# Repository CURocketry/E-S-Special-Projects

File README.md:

# E&S Special Projects
This is where all the non-payload or research related E&S projects go. Below you can find a list and short description of all projects in this repo. 
## Airbrake
All E&S work on the airbrake project. 
## ES Datalogger
All purpose datalogger for model rockets. Logs data from a 9-DoF IMU and altimeter and saves it to an SD card. Powered by a 3.7V LiPo battery.
## SAMD21 Minimal
Minimal circiut that has all the hardware needed to run and program a SAMD21 chip. Be sure to add a USB header if you want to program via USB!

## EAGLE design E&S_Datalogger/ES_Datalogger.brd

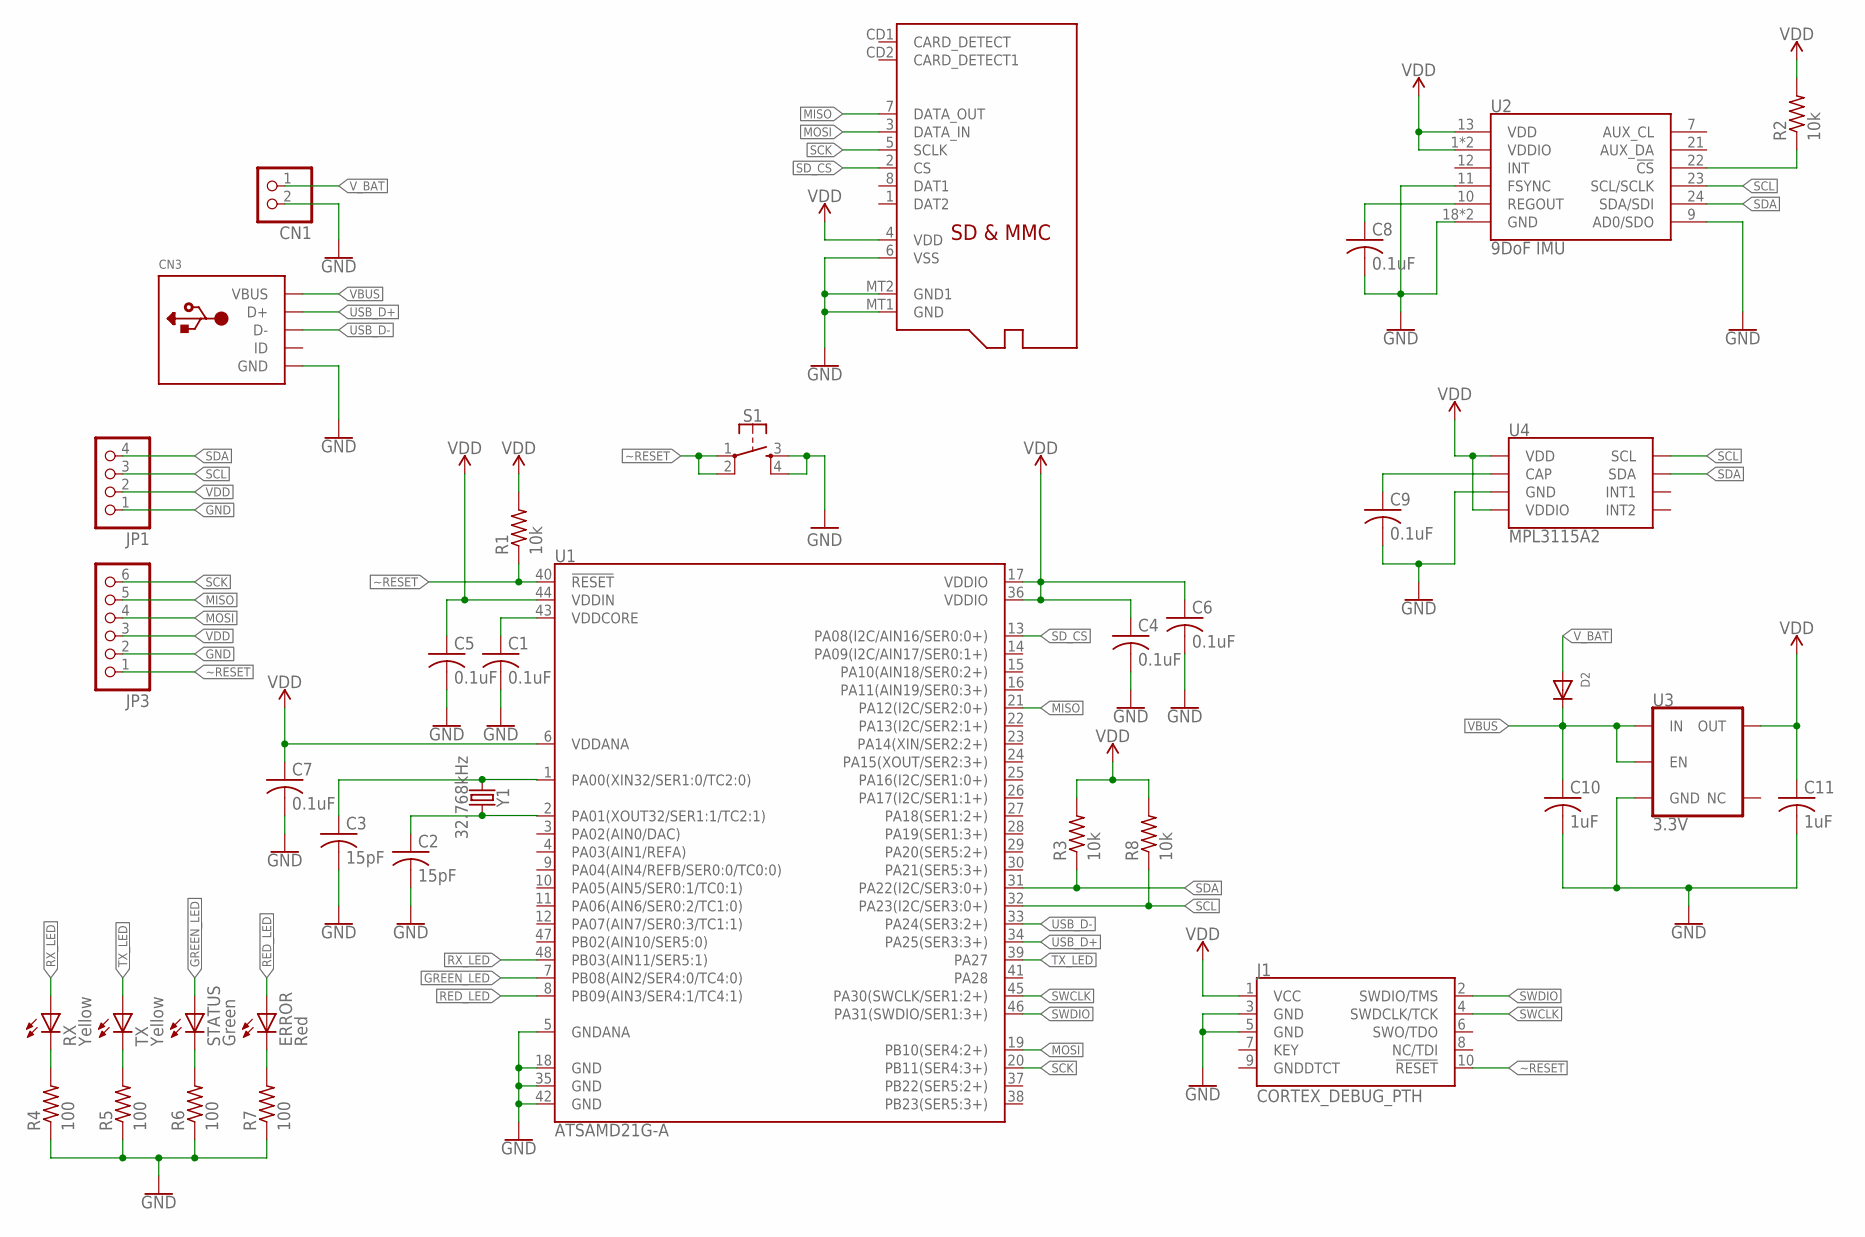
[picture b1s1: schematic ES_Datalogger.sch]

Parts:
C1, C4, C5, C6, C7, C8, C9: 0.1uF; C0805
C2, C3: 15pF; C0805
C10, C11: 1uF; C0805
CN1: JST_2PIN-SMT; JST-PH-2-SMT
CN3: USBMOLEX; USB-MINIB-THM-MOLEX
D2: DIODE_SOD-123FL; SOD-123FL
ERROR: Red; CHIPLED_0805
J1: CORTEX_DEBUG_PTH; 2X5-PTH-1.27MM
JP1: PINHD-1X4; 1X04
JP3: PINHD-1X6; 1X06
R1, R2, R3, R8: 10k; R0805
R4, R5, R6, R7: 100; R0805
RX: Yellow; CHIPLED_0805
S1: MOMENTARY-SWITCH-SPST-2-SMD-5.2MM; TACTILE_SWITCH_SMD_5.2MM
STATUS: Green; CHIPLED_0805
TX: Yellow; CHIPLED_0805
U1: ATSAMD21G-A; TQFP-48
U2: 9DoF IMU; QFN24-3X3
U3: 3.3V; SOT23-5
U4: MPL3115A2; LGA-8-5X3
U$1: MICROSD
Y1: 32.768kHz; CRYSTAL-SMD-MC-146

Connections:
GND: C1.2, C2.2, C3.2, C4.2, C5.2, C6.2, C7.2, C8.2, C9.2, C10.2, C11.2, CN1.2 (1), CN3.GND, J1.3 (GND), J1.5 (GND), JP1.1, JP3.2, R4.1, R5.1, R6.1, R7.1, S1.3, S1.4, U1.5 (GNDANA), U1.18 (GND), U1.35 (GND), U1.42 (GND), U2.9 (AD0/SDO), U2.11 (FSYNC), U2.18 (GND), U2.20 (GND), U3.2 (GND), U4.3 (GND), U$1.6 (VSS), U$1.MT1 (GND), U$1.MT2 (GND1)
GREEN_LED: STATUS.A, U1.7 (PB08(AIN2/SER4:0/TC4:0))
MISO: JP3.5, U1.21 (PA12(I2C/SER2:0+)), U$1.7 (DATA_OUT)
MOSI: JP3.4, U1.19 (PB10(SER4:2+)), U$1.3 (DATA_IN)
unnamed: C1.1, U1.43 (VDDCORE)
unnamed: C2.1, U1.2 (PA01(XOUT32/SER1:1/TC2:1)), Y1.P$1 (2)
unnamed: R4.2, RX.C
unnamed: C3.1, U1.1 (PA00(XIN32/SER1:0/TC2:0)), Y1.P$2 (1)
unnamed: R5.2, TX.C
unnamed: R6.2, STATUS.C
unnamed: ERROR.C, R7.2
unnamed: C9.1, U4.2 (CAP)
unnamed: R2.1, U2.22 (!CS)
unnamed: C8.1, U2.10 (REGOUT)
RED_LED: ERROR.A, U1.8 (PB09(AIN3/SER4:1/TC4:1))
RX_LED: RX.A, U1.48 (PB03(AIN11/SER5:1))
SCK: JP3.6, U1.20 (PB11(SER4:3+)), U$1.5 (SCLK)
SCL: JP1.3, R8.1, U1.32 (PA23(I2C/SER3:0+)), U2.23 (SCL/SCLK), U4.8 (SCL)
SDA: JP1.4, R3.1, U1.31 (PA22(I2C/SER3:0+)), U2.24 (SDA/SDI), U4.7 (SDA)
SD_CS: U1.13 (PA08(I2C/AIN16/SER0:0+)), U$1.2 (CS)
SWCLK: J1.4 (SWDCLK/TCK), U1.45 (PA30(SWCLK/SER1:2+))
SWDIO: J1.2 (SWDIO/TMS), U1.46 (PA31(SWDIO/SER1:3+))
TX_LED: TX.A, U1.39 (PA27)
USB_D+: CN3.D+, U1.34 (PA25(SER3:3+))
USB_D-: CN3.D-, U1.33 (PA24(SER3:2+))
VBUS: C10.1, CN3.VBUS, D2.C, U3.1 (IN), U3.3 (EN)
VDD: C4.1, C5.1, C6.1, C7.1, C11.1, J1.1 (VCC), JP1.2, JP3.3, R1.2, R2.2, R3.2, R8.2, U1.6 (VDDANA), U1.17 (VDDIO), U1.36 (VDDIO), U1.44 (VDDIN), U2.1 (VDDIO), U2.8 (VDDIO), U2.13 (VDD), U3.5 (OUT), U4.1 (VDD), U4.4 (VDDIO), U$1.4 (VDD)
V_BAT: CN1.1 (2), D2.A
~RESET: J1.10 (!RESET), JP3.1, R1.1, S1.1, S1.2, U1.40 (!RESET!)

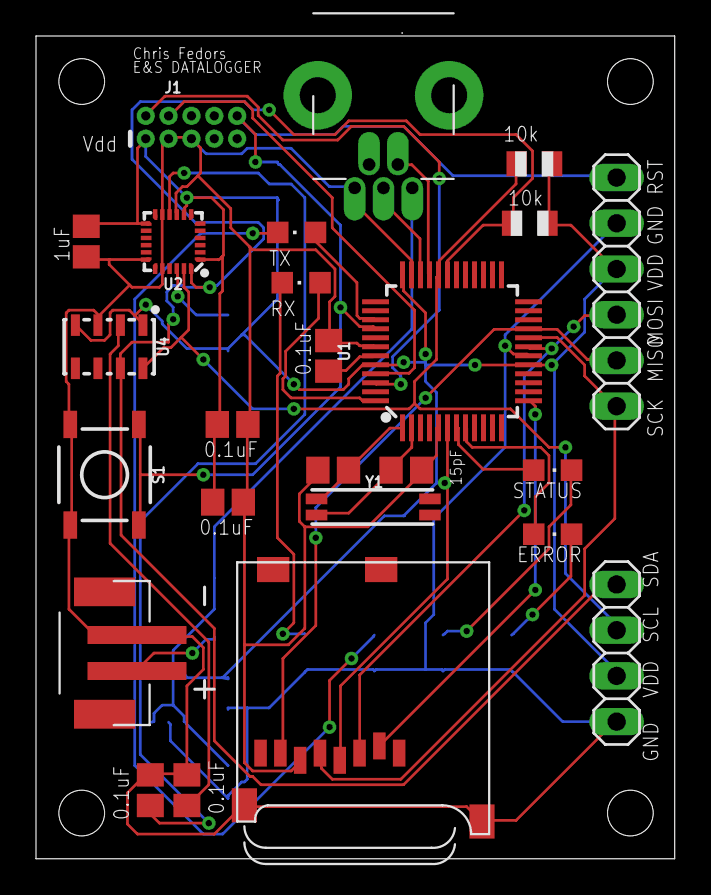
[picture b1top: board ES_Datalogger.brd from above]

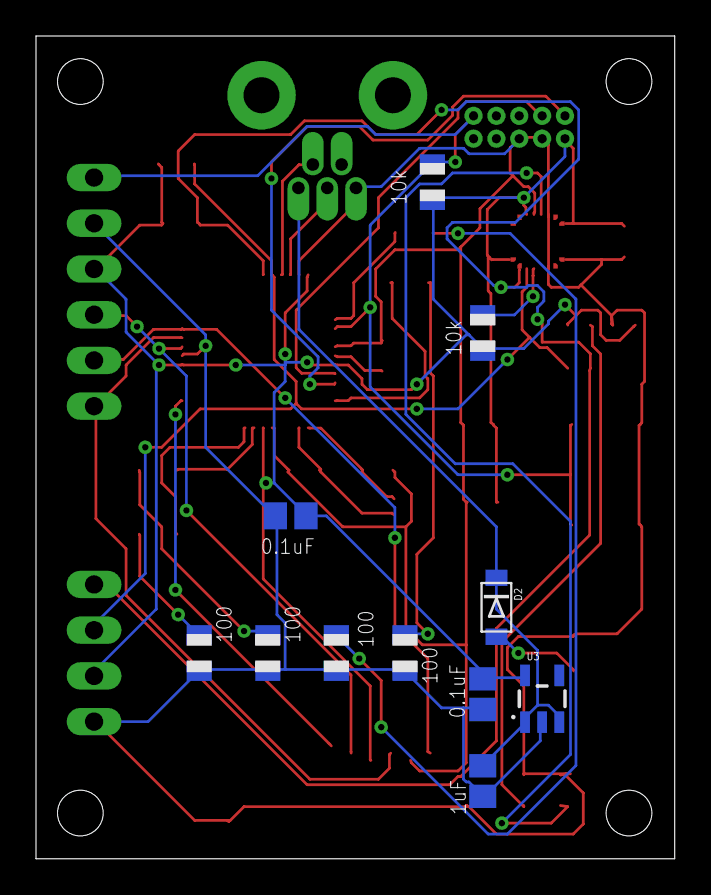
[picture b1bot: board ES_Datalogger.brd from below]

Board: 2 copper layers, 35.5 x 45.7 mm, 36 parts (11 on the bottom side), 29 nets.

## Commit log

2018-04-26 Added Schematic and BOM for SAMD21 minimal board
2018-04-26 Created Folder for SAMD21
2018-04-28 Added E&S Datalogger schematic
2018-05-01 Added board file
2018-05-02 Finished Datalogging Board
2018-05-03 Finished board and BoM
2018-05-06 Create airbrake-minimal.sch
    the power stuff needs to be fixed but
2018-05-06 Changed names, added datalogger code
2018-05-06 Gave airbrake its own folder

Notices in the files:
parts and their libraries:
SparkFun-Connectors: Licensing: Creative Commons ShareAlike 4.0 International - https://creativecommons.org/licenses/by-sa/4.0
